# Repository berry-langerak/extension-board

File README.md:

View this project on [CADLAB.io](https://cadlab.io/project/23659). 

# Nanobrew extension board

This is an extension board for a Raspberry PI, to wire DS18B20 temperature
sensors, and various actors (up to 16!) without a spagetthi-like mess.

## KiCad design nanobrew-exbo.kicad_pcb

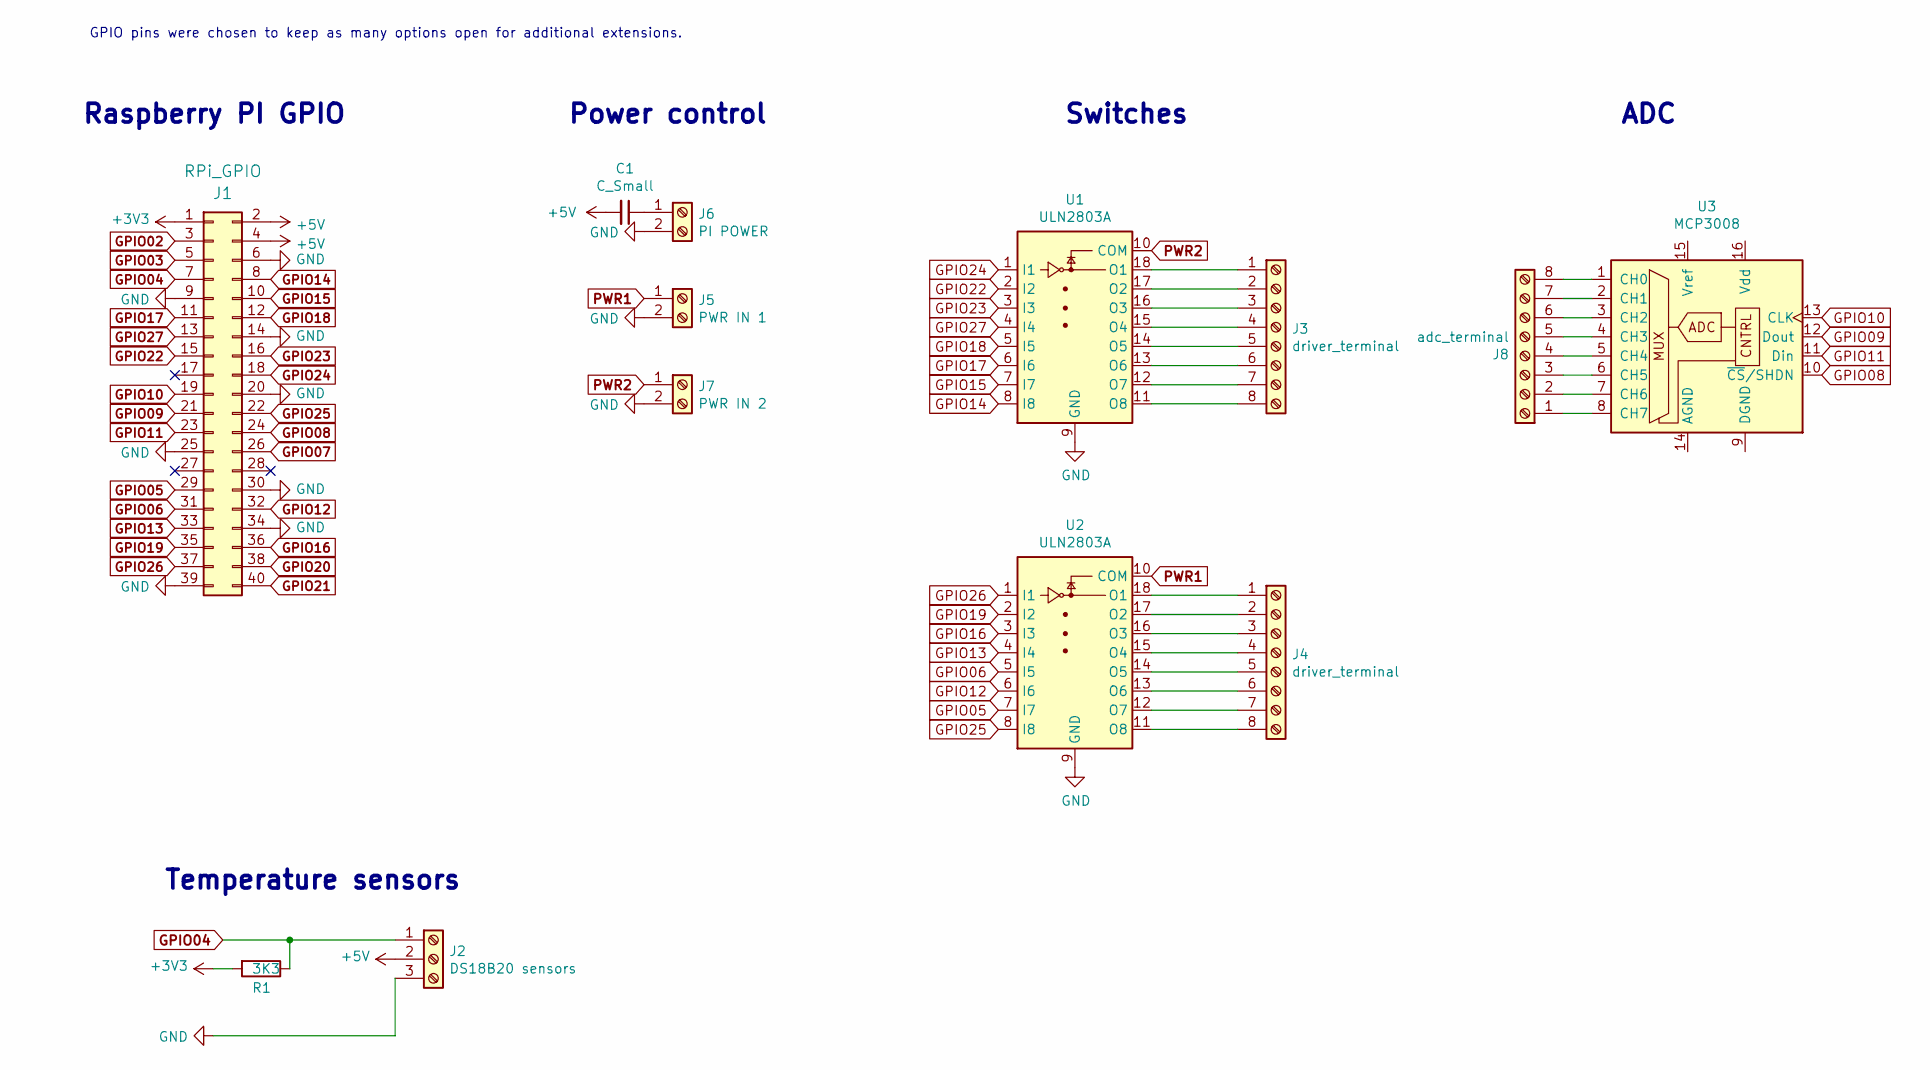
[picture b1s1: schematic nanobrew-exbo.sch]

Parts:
C1: C_Small; CP_Radial_D4.0mm_P2.00mm
J1: RPi_GPIO; PinHeader_2x20_P2.54mm_Vertical
J2: DS18B20 sensors; TerminalBlock_TE_282834-3_1x03_P2.54mm_Horizontal
J3, J4: driver_terminal; TerminalBlock_TE_282834-8_1x08_P2.54mm_Horizontal
J5: PWR IN 1; TerminalBlock_TE_282834-2_1x02_P2.54mm_Horizontal
J6: PI POWER; TerminalBlock_TE_282834-2_1x02_P2.54mm_Horizontal
J7: PWR IN 2; TerminalBlock_TE_282834-2_1x02_P2.54mm_Horizontal
J8: adc_terminal; TerminalBlock_TE_282834-8_1x08_P2.54mm_Horizontal
R1: 3K3; R_Axial_DIN0204_L3.6mm_D1.6mm_P5.08mm_Horizontal
U1, U2: ULN2803A; DIP-18_W7.62mm
U3: MCP3008; DIP-16_W7.62mm

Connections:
+3V3: J1.1, R1.2
+5V: C1.2, J1.2, J1.4, J2.2
GND: J1.6, J1.9, J1.14, J1.20, J1.25, J1.30, J1.34, J1.39, J2.3, J5.2, J6.2, J7.2, U1.9 (GND), U2.9 (GND)
GPIO02: J1.3
GPIO03: J1.5
GPIO04: J1.7, J2.1, R1.1
GPIO05: J1.29, U2.7 (I7)
GPIO06: J1.31, U2.5 (I5)
GPIO07: J1.26
GPIO08: J1.24, U3.10 (~CS~/SHDN)
GPIO09: J1.21, U3.12 (Dout)
GPIO10: J1.19, U3.13 (CLK)
GPIO11: J1.23, U3.11 (Din)
GPIO12: J1.32, U2.6 (I6)
GPIO13: J1.33, U2.4 (I4)
GPIO14: J1.8, U1.8 (I8)
GPIO15: J1.10, U1.7 (I7)
GPIO16: J1.36, U2.3 (I3)
GPIO17: J1.11, U1.6 (I6)
GPIO18: J1.12, U1.5 (I5)
GPIO19: J1.35, U2.2 (I2)
GPIO20: J1.38
GPIO21: J1.40
GPIO22: J1.15, U1.2 (I2)
GPIO23: J1.16, U1.3 (I3)
GPIO24: J1.18, U1.1 (I1)
GPIO25: J1.22, U2.8 (I8)
GPIO26: J1.37, U2.1 (I1)
GPIO27: J1.13, U1.4 (I4)
unnamed: C1.1, J6.1
unnamed: J3.1, U1.18 (O1)
unnamed: J3.2, U1.17 (O2)
unnamed: J3.3, U1.16 (O3)
unnamed: J3.4, U1.15 (O4)
unnamed: J3.5, U1.14 (O5)
unnamed: J3.6, U1.13 (O6)
unnamed: J3.7, U1.12 (O7)
unnamed: J3.8, U1.11 (O8)
unnamed: J4.1, U2.18 (O1)
unnamed: J4.2, U2.17 (O2)
unnamed: J4.3, U2.16 (O3)
unnamed: J4.4, U2.15 (O4)
unnamed: J4.5, U2.14 (O5)
unnamed: J4.6, U2.13 (O6)
unnamed: J4.7, U2.12 (O7)
unnamed: J4.8, U2.11 (O8)
unnamed: J8.1, U3.8 (CH7)
unnamed: J8.2, U3.7 (CH6)
unnamed: J8.3, U3.6 (CH5)
unnamed: J8.4, U3.5 (CH4)
unnamed: J8.5, U3.4 (CH3)
unnamed: J8.6, U3.3 (CH2)
unnamed: J8.7, U3.2 (CH1)
unnamed: J8.8, U3.1 (CH0)
PWR1: J5.1, U2.10 (COM)
PWR2: J7.1, U1.10 (COM)

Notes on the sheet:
Raspberry PI GPIO
Switches
Temperature sensors
Power control
ADC
GPIO pins were chosen to keep as many options open for additional extensions.

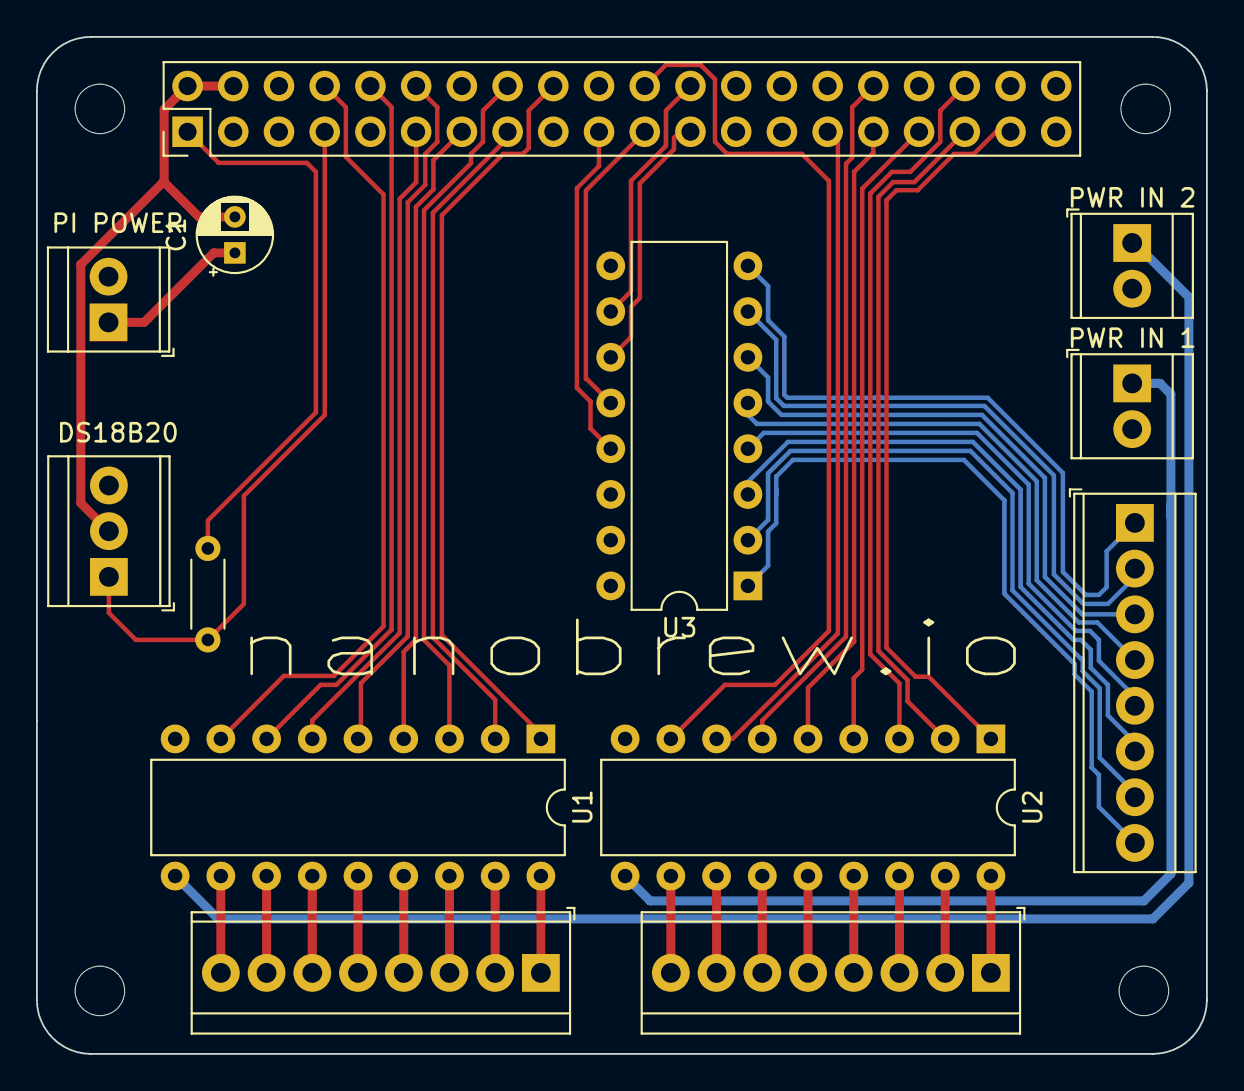
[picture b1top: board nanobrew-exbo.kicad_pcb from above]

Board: 2 copper layers, 65.0 x 56.5 mm, 13 parts (0 on the bottom side), 51 nets.

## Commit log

2020-12-17 Initial commit.
2020-12-17 Adding capacitor
2020-12-17 Adjusting README.
2020-12-17 Backlink to CADLAB.io has been added.
2020-12-17 Removing old files.
2020-12-17 Adding a ground plane.
